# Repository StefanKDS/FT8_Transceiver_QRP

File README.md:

# FT8 Transceiver

My QRP FT8 Transceiver is basded on a ATS20+ Receiver and on the FT8 project on the website https://www.elektronik-labor.de/HF/FT8QRP.html .

The new Firmware of the ATS20+ is based on the firmware from Goshante: https://github.com/goshante/ats20_ats_ex .  
The Firmware of the TX part is based on these project: https://www.elektronik-labor.de/HF/FT8QRP.html .
You can find the documentation of the TX code here: https://github.com/StefanKDS/FT8_Transceiver_QRP/blob/main/ATS_EX_FT8_TX/Documentation/FT8_TX_Documentation.pdf

I made modifications on both source codes.

Please note that the Microcontroller of the TX part has to be a Nano, not a Nano R4, because I use the comperator input D6 / D7. The Nano R4 don't has these input.

The PA is a 2W PA from China. For this use it's totally OK.
In the end of these document you can find pictures of all parts I bought.

## Overview:

## Description:

On the ATS20+ Board we have to make some small modifications:

- Replace the Arduino Nano with a Arduino Nano R4. The "old" Nano you can use for the TX part.
- Remove the battery
- Remove U1 (TP4056).
- Upload the fimrware in the folder ATS_EX.

## Details:

## Used parts:
ATS20+

---------------------------------------------------------------------------------------------------

PowerUnit HW688

---------------------------------------------------------------------------------------------------

PA

At 12V VCC and 7Mhz / 1mW ( 0dBm ) input it has around +33dBm ( 2W )

---------------------------------------------------------------------------------------------------

LPF

---------------------------------------------------------------------------------------------------

Relais

---------------------------------------------------------------------------------------------------

Si5351

---------------------------------------------------------------------------------------------------

Nano R4

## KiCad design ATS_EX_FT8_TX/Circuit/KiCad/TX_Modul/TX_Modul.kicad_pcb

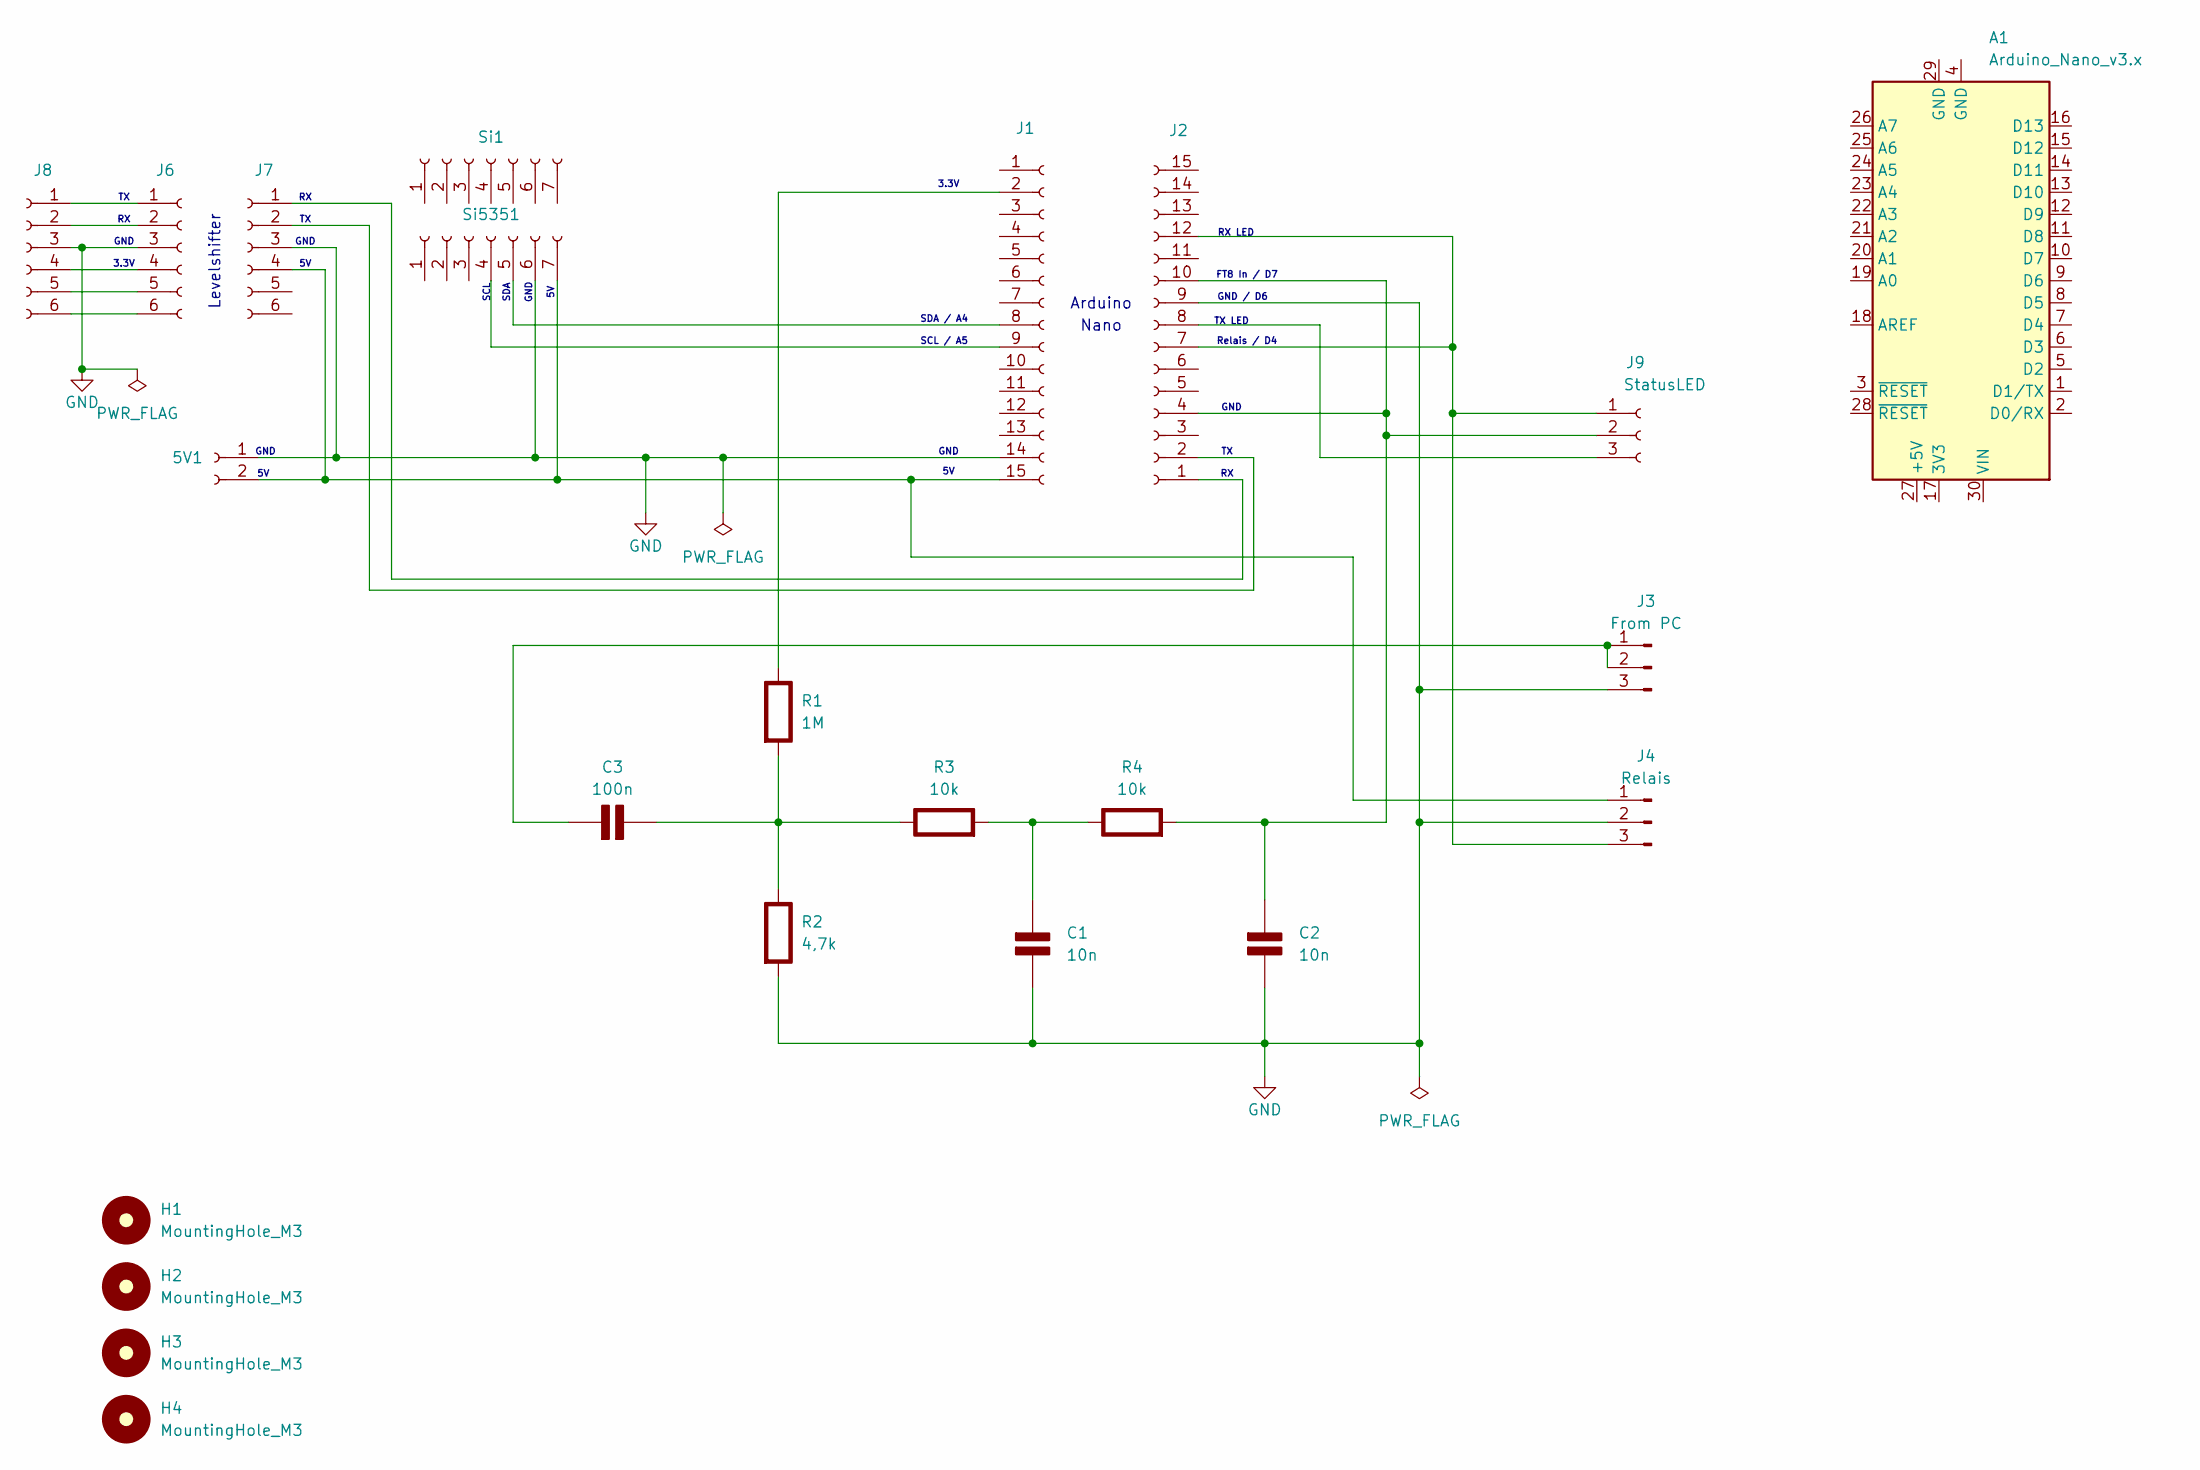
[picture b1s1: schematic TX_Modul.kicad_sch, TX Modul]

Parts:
5V1: Conn_01x02_Socket; PinSocket_1x02_P2.54mm_Vertical
A1: Arduino_Nano_v3.x; Arduino_Nano
C1, C2: 10n; C_Disc_D4.7mm_W2.5mm_P5.00mm; Rating V
C3: 100n; C_Disc_D4.7mm_W2.5mm_P5.00mm; Rating V
H1, H2, H3, H4: MountingHole_M3; MountingHole_3.2mm_M3
J1, J2: Conn_01x15_Socket; PinSocket_1x15_P2.54mm_Vertical
J3: From PC; PinHeader_1x03_P2.54mm_Vertical
J4: Relais; PinHeader_1x03_P2.54mm_Vertical
J6, J7, J8: Conn_01x06_Socket; PinSocket_1x06_P2.54mm_Vertical
J9: StatusLED; PinSocket_1x03_P2.54mm_Vertical
R1: 1M; R_Axial_DIN0204_L3.6mm_D1.6mm_P7.62mm_Horizontal; Rating W
R2: 4,7k; R_Axial_DIN0204_L3.6mm_D1.6mm_P7.62mm_Horizontal; Rating W
R3, R4: 10k; R_Axial_DIN0204_L3.6mm_D1.6mm_P7.62mm_Horizontal; Rating W
Si1, Si5351: Conn_01x07_Socket; PinSocket_1x07_P2.54mm_Vertical

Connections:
GND: 5V1.1, C1.2 (-), C2.2 (-), J1.14, J2.9, J3.3, J4.2, J6.3, J7.3, J8.3, R2.2 (-), Si5351.6
unnamed: 5V1.2, J1.15, J4.1, J7.4, Si5351.7
unnamed: C1.1 (+), R3.2 (-), R4.1 (+)
unnamed: C2.1 (+), J2.4, J2.10, J9.2, R4.2 (-)
unnamed: C3.1 (+), J3.1, J3.2
unnamed: C3.2 (-), R1.2 (-), R2.1 (+), R3.1 (+)
unnamed: J1.2, R1.1 (+)
unnamed: J1.8, Si5351.5
unnamed: J1.9, Si5351.4
unnamed: J2.1, J7.1
unnamed: J2.2, J7.2
unnamed: J2.8, J9.3
unnamed: J2.7, J2.12, J4.3, J9.1
unnamed: J6.1, J8.1
unnamed: J6.2, J8.2
unnamed: J6.4, J8.4
unnamed: J6.5, J8.5
unnamed: J6.6, J8.6

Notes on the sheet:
GND
Arduino
GND / D6
Relais / D4
SCL
SDA / A4
RX LED
Levelshifter
FT8 In / D7
SDA
3.3V
TX LED
SCL / A5
Nano

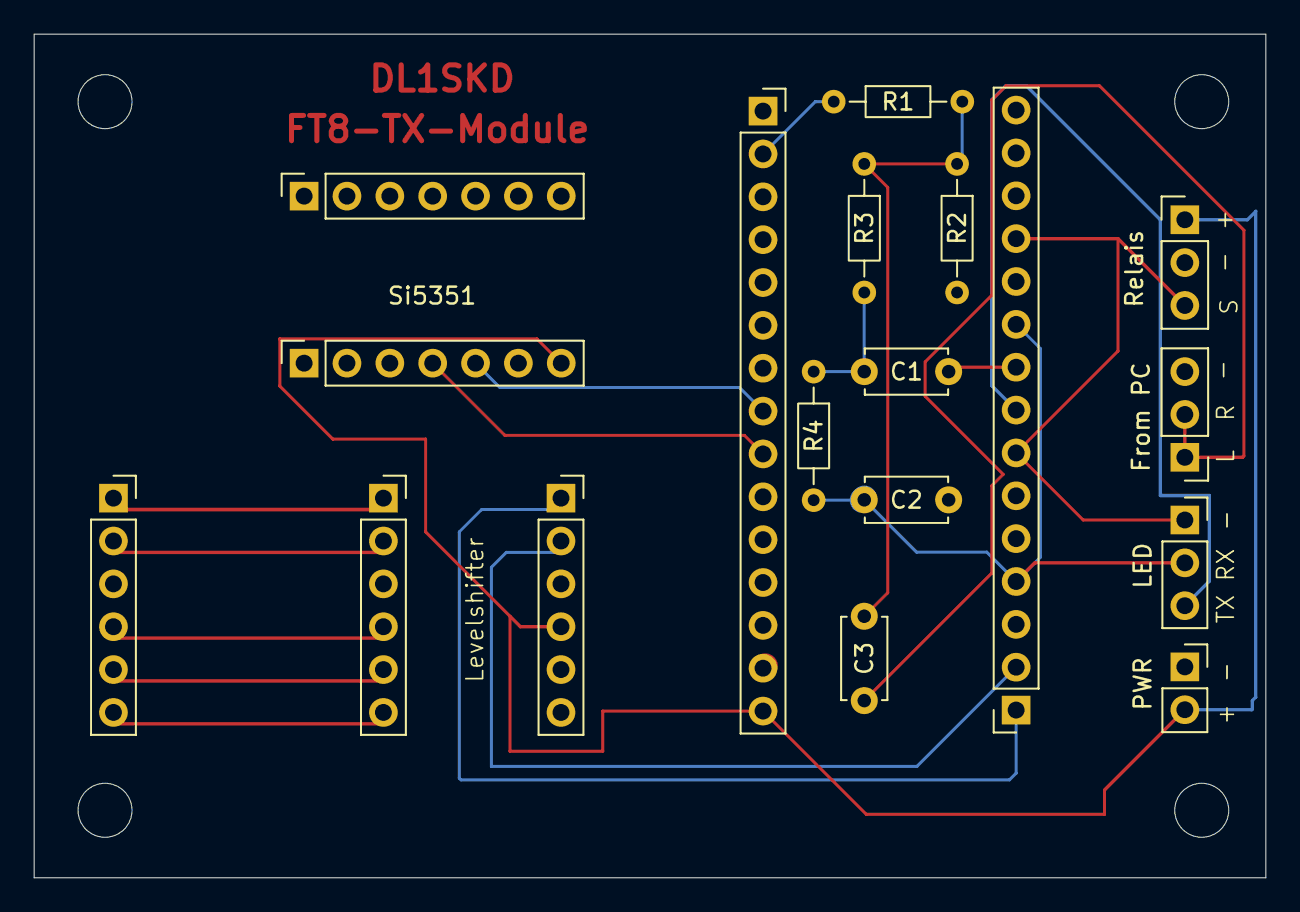
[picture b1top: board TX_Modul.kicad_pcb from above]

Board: 2 copper layers, 73.0 x 50.0 mm, 22 parts (0 on the bottom side), 18 nets.

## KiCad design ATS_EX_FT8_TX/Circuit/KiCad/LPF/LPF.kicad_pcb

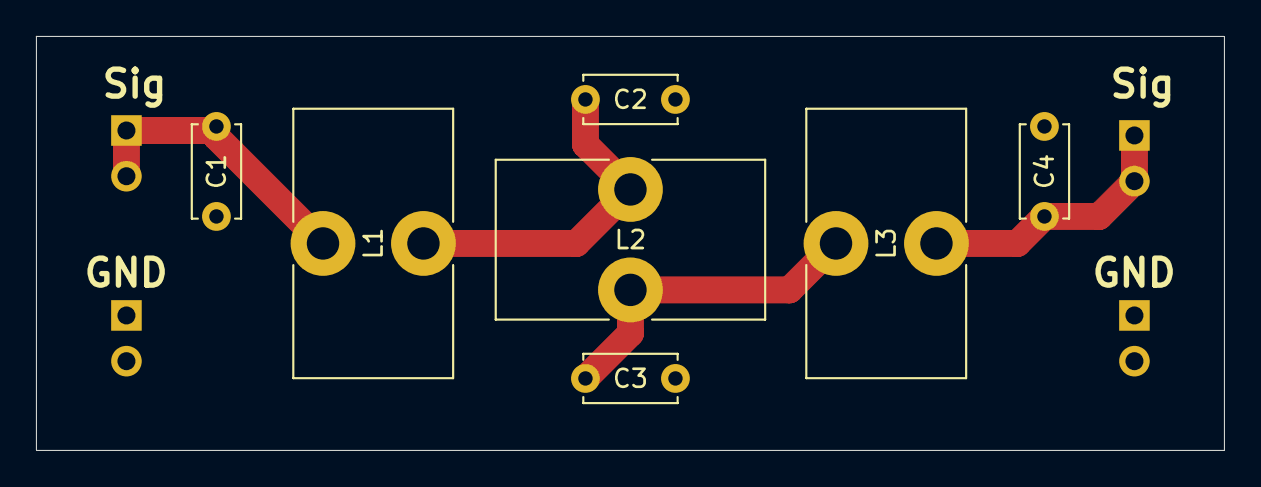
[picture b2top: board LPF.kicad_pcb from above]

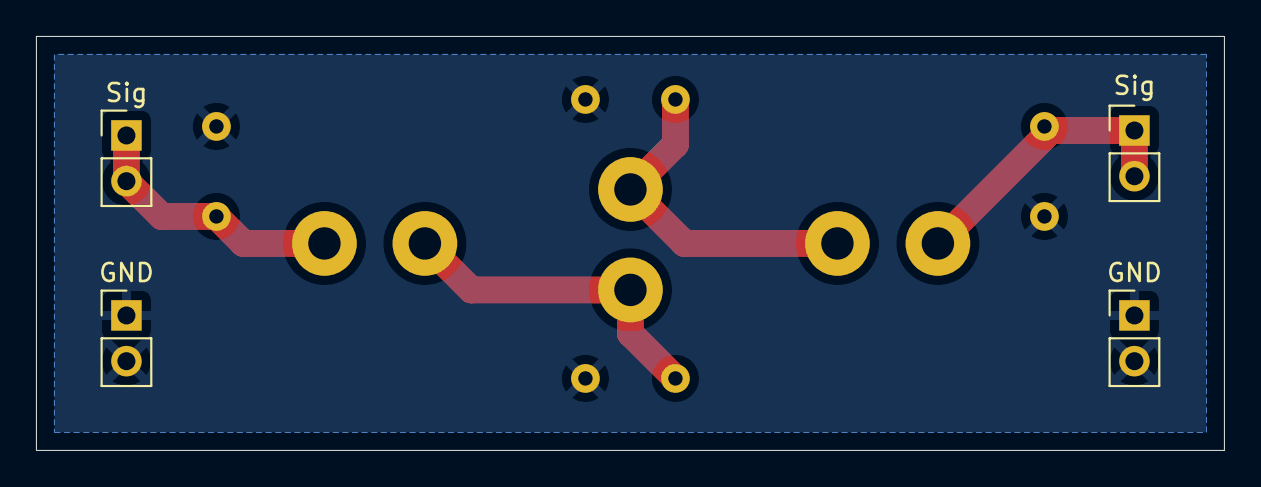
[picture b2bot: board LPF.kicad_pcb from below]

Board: 2 copper layers, 66.0 x 23.0 mm, 11 parts (4 on the bottom side), 5 nets.

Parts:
C1, C2, C3, C4: C; C_Disc_D5.0mm_W2.5mm_P5.00mm
GND: Conn_01x02_Pin; PinHeader_1x02_P2.54mm_Vertical
GND#2: Conn_01x02_Pin; PinHeader_1x02_P2.54mm_Vertical
L1, L2, L3: L_Iron; L_Toroid_Vertical_L14.7mm_W8.6mm_P5.58mm_Pulse_KM-1
Sig: Conn_01x02_Pin; PinHeader_1x02_P2.54mm_Vertical
Sig#2: Conn_01x02_Pin; PinHeader_1x02_P2.54mm_Vertical

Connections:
GND: C1.2 (-), C2.2 (-), C3.2 (-), C4.2 (-), GND.1, GND.2, GND#2.1, GND#2.2
unnamed: C1.1 (+), L1.1, Sig.1, Sig.2
unnamed: C2.1 (+), L1.2, L2.1
unnamed: C3.1 (+), L2.2, L3.1
unnamed: C4.1 (+), L3.2, Sig#2.1, Sig#2.2

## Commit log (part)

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2025-12-04 Auf R4 umgestellt
2025-12-04 Doku
2025-12-04 FT8 vorbereitung
2025-12-04 Changed Doku
2025-12-05 Anpassungen
2025-12-06 SI5351 implementiert
2025-12-08 UART implementiert mit Befehlen
    Freq => NANO R4
    NANO <= TX 1/0
2025-12-08 test
2025-12-08 Relais & TX an RX
2025-12-10 Schematic
2025-12-12 Korrektur
2026-01-01 KiCad Projekt
2026-01-04 Docs
2026-01-04 NewOrder
2026-01-04 Revise README for FT8 Transceiver firmware update
    Updated the README to reflect changes in the firmware and features for the FT8 Transceiver based on ATS-20+ Receiver.
2026-01-04 Update README with project description
    Corrected the title and added a brief description of the transceiver.
2026-01-05 pics
2026-01-05 rotate
2026-01-05 Add overview section to README
    Added an overview section with a placeholder for an image.
2026-01-05 Revise README for FT8 Transceiver modifications
    Updated README with new firmware and modification details for ATS20+ transceiver.
2026-01-05 Update README with microcontroller specifications
    Clarify microcontroller requirements for TX part.
2026-01-05 Refactor for Nano R4 compatibility and clean up code
    Refactor code to replace direct register usage with Arduino API for better compatibility with Nano R4. Removed conditional compilation for RDS-related features and updated comments for clarity.
2026-01-05 Update app version and display text in ATS_EX
2026-01-11 Code documentation
2026-01-13 FT8 Circuit
2026-01-13 Circuit
2026-01-14 Remove image 005 from README
    Removed an image from the README.
2026-01-14 Add image 005 to README details
    Added an additional image to the details section.
2026-01-14 Enhance code clarity with comments on timing and frequency
    Added comments for clarity on timer resets and frequency calculations.
2026-01-20 LPF Circuit
2026-01-21 KiCad
2026-01-22 TXModul KiCad
2026-01-23 Update README with PA output details
    Added power output information for the PA section.
2026-01-23 Update PA power rating in README
    Corrected the power rating of the PA from 3W to 2W.
2026-01-23 LPF update
2026-02-04 Documentation
2026-02-04 Update README with TX code documentation link
    Added documentation link for TX code.
2026-02-04 Add LPF schematic image to README
    Added LPF schematic image to the README.
2026-02-13 update KiCad TX Module
2026-02-13 Update Platine
2026-02-14 Update TX PCB
2026-03-23 Update Schematic
2026-06-16 Gerber
